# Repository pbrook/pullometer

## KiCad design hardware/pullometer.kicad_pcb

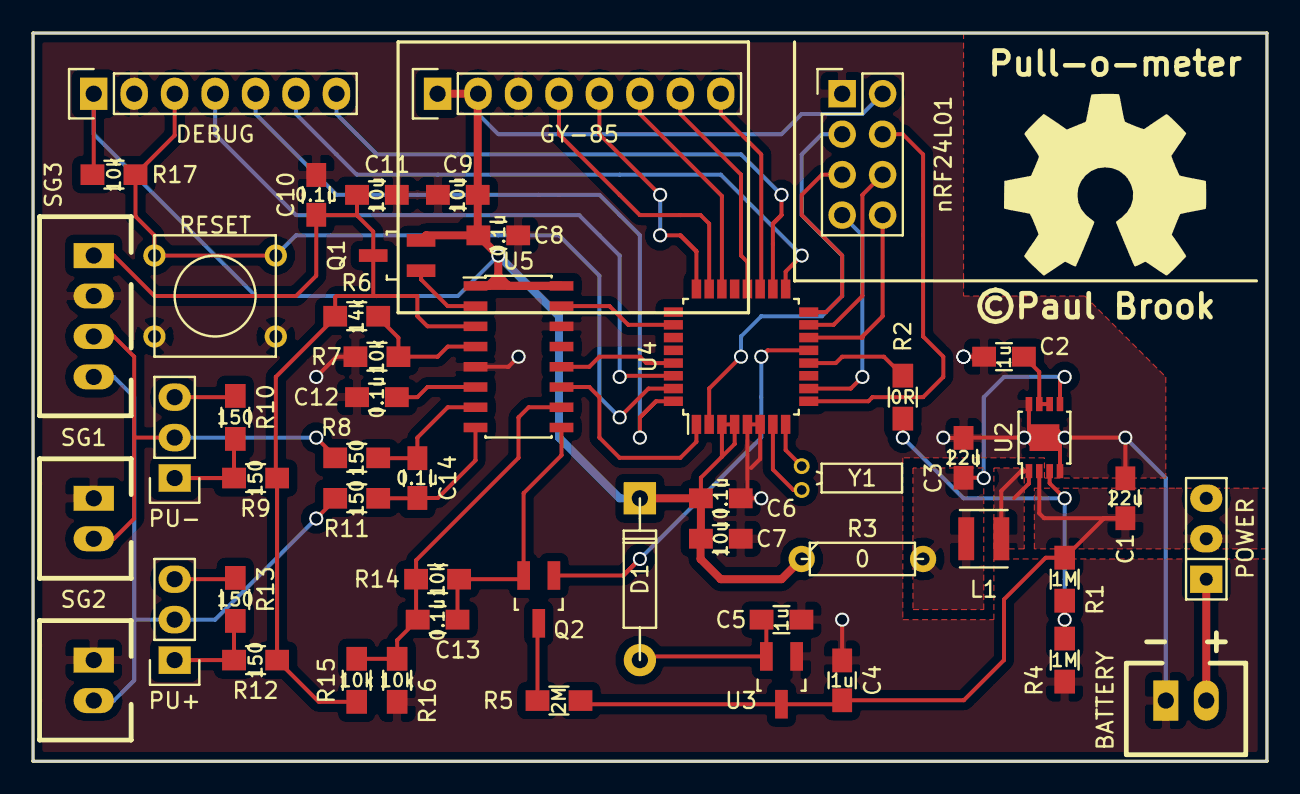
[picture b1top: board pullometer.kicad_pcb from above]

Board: 2 copper layers, 77.5 x 45.7 mm, 51 parts (0 on the bottom side), 47 nets.

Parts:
C1, C3: 22u; C_0805_HandSoldering_V
C2, C4, C5: 1u; C_0805_HandSoldering_V
C6, C8, C10, C12, C13, C14: 0.1u; C_0805_HandSoldering_V
C7, C9, C11: 10u; C_0805_HandSoldering_V
D1: 1n4001; DO-41
JP1: PU-; Pin_Header_Straight_1x03
JP2: PU+; Pin_Header_Straight_1x03
L1: 4.7uH; Neosid_Inductor_SMS-ME3015
P1: BATTERY; JST-XH-2
P2: SG1; JST-XH-2
P3: SG2; JST-XH-2
P4: DEBUG; Pin_Header_Straight_1x07
P5: SG3; JST-XH-4
Q1: MMBT4403; SOT-23_Handsoldering
Q2: TMS2302CX; SOT-23_Handsoldering
R1, R4: 1M; R_0805_HandSoldering_V
R2: 0R; R_0805_HandSoldering_V
R3: 0; R3-LARGE_PADS
R5: 2M; R_0805_HandSoldering_V
R6: 14k; R_0805_HandSoldering_V
R7, R14, R15, R16, R17: 10k; R_0805_HandSoldering_V
R8, R9, R10, R11, R12, R13: 150; R_0805_HandSoldering_V
SW1: RESET; SW_PUSH_SMALL
SW2: POWER; SW_Micro_SPST
U1: nRF24L01; Pin_Header_Straight_2x04
U2: LTC3621; MSOP-8-1EP_3x3mm_Pitch0.65mm
U3: MCP1702; SOT-23_Handsoldering
U4: MKL05Z32VLC4; LQFP-32_7x7mm_Pitch0.8mm
U5: HX711; SOIC-16_3.9x9.9mm_Pitch1.27mm
U6: GY-85; Socket_Strip_Straight_1x08
Y1: 32.768kHz; Crystal_Round_Horizontal_2mm

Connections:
+3V3: C6.1, C7.1, C8.1, C9.1, D1.1, P4.1, Q1.2, R3.1, R17.1, U1.2, U4.3, U4.4, U5.1, U5.16, U6.1, U6.2
/BAT_EN: Q2.1, U4.13
/E+: C10.1, C11.1, P5.1, Q1.3, R6.1, R9.2, R12.2, R15.2, U5.3
/HX_DATA: U4.29, U5.12
/HX_RATE: U4.26, U5.15
/HX_SCK: U4.1, U5.11
/IN+: JP2.2, P3.2, P5.4, R11.2
/IN-: JP1.2, P2.2, P5.3, R8.2
/INT_A: U4.20, U6.7
/INT_G: U4.19, U6.8
/INT_M: U4.22, U6.6
/MISO: U1.7, U4.10
/MOSI: U1.6, U4.15
/RF_CE: U1.3, U4.2
/RF_CS: U1.4, U4.9
/RF_IRQ: U1.8, U4.14
/RUN: R1.2, R2.2, R4.1, U2.3
/SCK: U1.5, U4.16
/SCL: U4.23, U6.4
/SDA: U4.24, U6.5
/SW: L1.2, U2.1
/SWD_CLK: P4.4, U4.30
/SWD_DIO: P4.5, U4.32
/SWD_RESET: P4.3, R17.2, SW1.1, U4.31
/S_RUN: R2.1, U4.12
/UART_RX: P4.6, U4.17
/UART_TX: P4.7, U4.18
/Vbat: C1.1, C4.1, R1.1, R5.1, SW2.2, U2.2, U3.3
/Vbuck: C3.1, L1.1, R3.2, U2.5
GND: C1.2, C2.2, C3.2, C4.2, C5.2, C6.2, C7.2, C8.2, C9.2, C10.2, C11.2, C12.2, P1.1, P2.1, P3.1, P4.2, P5.2, R4.2, R7.2, R16.2, SW1.2, U1.1, U2.4, U2.8, U2.9, U3.1, U4.5, U4.6, U5.5, U5.14, U6.3
unnamed: C2.1, U2.6, U2.7
unnamed: C5.1, D1.2, U3.2
unnamed: C12.1, U5.6
unnamed: C13.1, Q2.2, R14.1, U5.9
unnamed: C13.2, R14.2, R15.1, R16.1, U5.10
unnamed: C14.1, R11.1, U5.8
unnamed: C14.2, R8.1, U5.7
unnamed: JP1.1, R9.1, R10.2
unnamed: JP1.3, R10.1
unnamed: JP2.1, R12.1, R13.2
unnamed: JP2.3, R13.1
unnamed: P1.2, SW2.1
unnamed: Q1.1, U5.2
unnamed: Q2.3, R5.2
unnamed: R6.2, R7.1, U5.4
unnamed: U4.7, Y1.2
unnamed: U4.8, Y1.1

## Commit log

2016-03-07 initial hardware design
2016-03-31 Production hardware
2016-05-22 Initial Firmware
    Basic accelerometer test.
2016-05-26 Initial strain gauge and accelerometer code.
2016-06-05 Initial Radio code.
2016-06-13 Inertial tracking and basic calibration.
2016-06-19 Better autocalibration.
2016-06-19 Reindent.
2016-06-19 Floating point debug
2016-06-19 Glitch filter on recalibration.
2016-06-20 Better recalibration
2016-07-03 Initial power management code.
2016-07-07 Sleep mode power saving tweaks
2016-07-17 Reindent

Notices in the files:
hardware/pullometer.kicad_pcb:
©Paul Brook
